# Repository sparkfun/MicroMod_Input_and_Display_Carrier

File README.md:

# SparkFun MicroMod Input and Display Carrier Board
========================================

[*SparkFun MicroMod Input and Display Carrier Board (16985)*](https://www.sparkfun.com/products/16985)

The SparkFun MicroMod Input and Display Carrier Board is a great way to add data and input visibility to your MicroMod project. Want to create your own embedded game? How about displaying data that is remotely collected and transmitted by your SparkFun MicroMod Weather Carrier Board and its processor? This is a great option. 

This carrier board combines a 2.4" TFT display, 6 addressable LEDs, onboard voltage regulator, a 6 pin IO connector, and microSD slot with the M.2 pin connector slot so that it can be used with compatible processor boards in our MicroMod ecosystem. 

Repository Contents
-------------------
* **/Firmware** - Example code specific to the Input and Display Carrier Board.
* **/Hardware** - Eagle design files (.brd, .sch)
* **/Production** - Production panel files (.brd)

Documentation
--------------
* **[Hookup Guide](https://learn.sparkfun.com/tutorials/sparkfun-micromod-input-and-display-carrier-board-hookup-guide)** - Basic hookup guide for the SparkFun MicroMod Input and Display Carrier Board.
* **[SparkFun Graphical Datasheets](https://github.com/sparkfun/Graphical_Datasheets)** -Graphical Datasheets for various SparkFun products.
* **[SparkFun HyperDisplay](https://github.com/sparkfun/SparkFun_HyperDisplay/archive/master.zip)** - Base level HyperDisplay library.
* **[SparkFun HyperDisplay ILI9341 Arduino Library](https://github.com/sparkfun/HyperDisplay_ILI9341_ArduinoLibrary/archive/master.zip)** - Mid level HyperDisplay library.
* **[SparkFun_HyperDisplay 4DLCD-320240 Arduino Library](https://github.com/sparkfun/HyperDisplay_4DLCD-320240_ArduinoLibrary/archive/master.zip)** -  Top level HyperDisplay library for the SparkFun MicroMod Input and Display Carrier Board. This library contains the examples for using the Input and Display Carrier Board.
* **[SparkFun MicroMod Button Arduino Library](https://github.com/sparkfun/SparkFun_MicroMod_Button_Arduino_Library)** - Example library to allow the user to determine if buttons on the board are pressed.  
* **[Getting Started with MicroMod](https://learn.sparkfun.com/tutorials/getting-started-with-micromod)** - A tutorial to help you get started with the MicroMod Ecosystem. 
* **[Designing with MicroMod](https://learn.sparkfun.com/tutorials/designing-with-micromod)** - A tutorial to walk you through the specs of the MicroMod processor and carrier board as well as the basics of incorporating the MicroMod form factor into your own PCB designs.

License Information
-------------------

This product is _**open source**_! 

Please review the LICENSE.md file for license information. 

If you have any questions or concerns on licensing, please contact technical support on our [SparkFun forums](https://forum.sparkfun.com/viewforum.php?f=152).

Distributed as-is; no warranty is given.

- Your friends at SparkFun.

_<COLLABORATION CREDIT>_

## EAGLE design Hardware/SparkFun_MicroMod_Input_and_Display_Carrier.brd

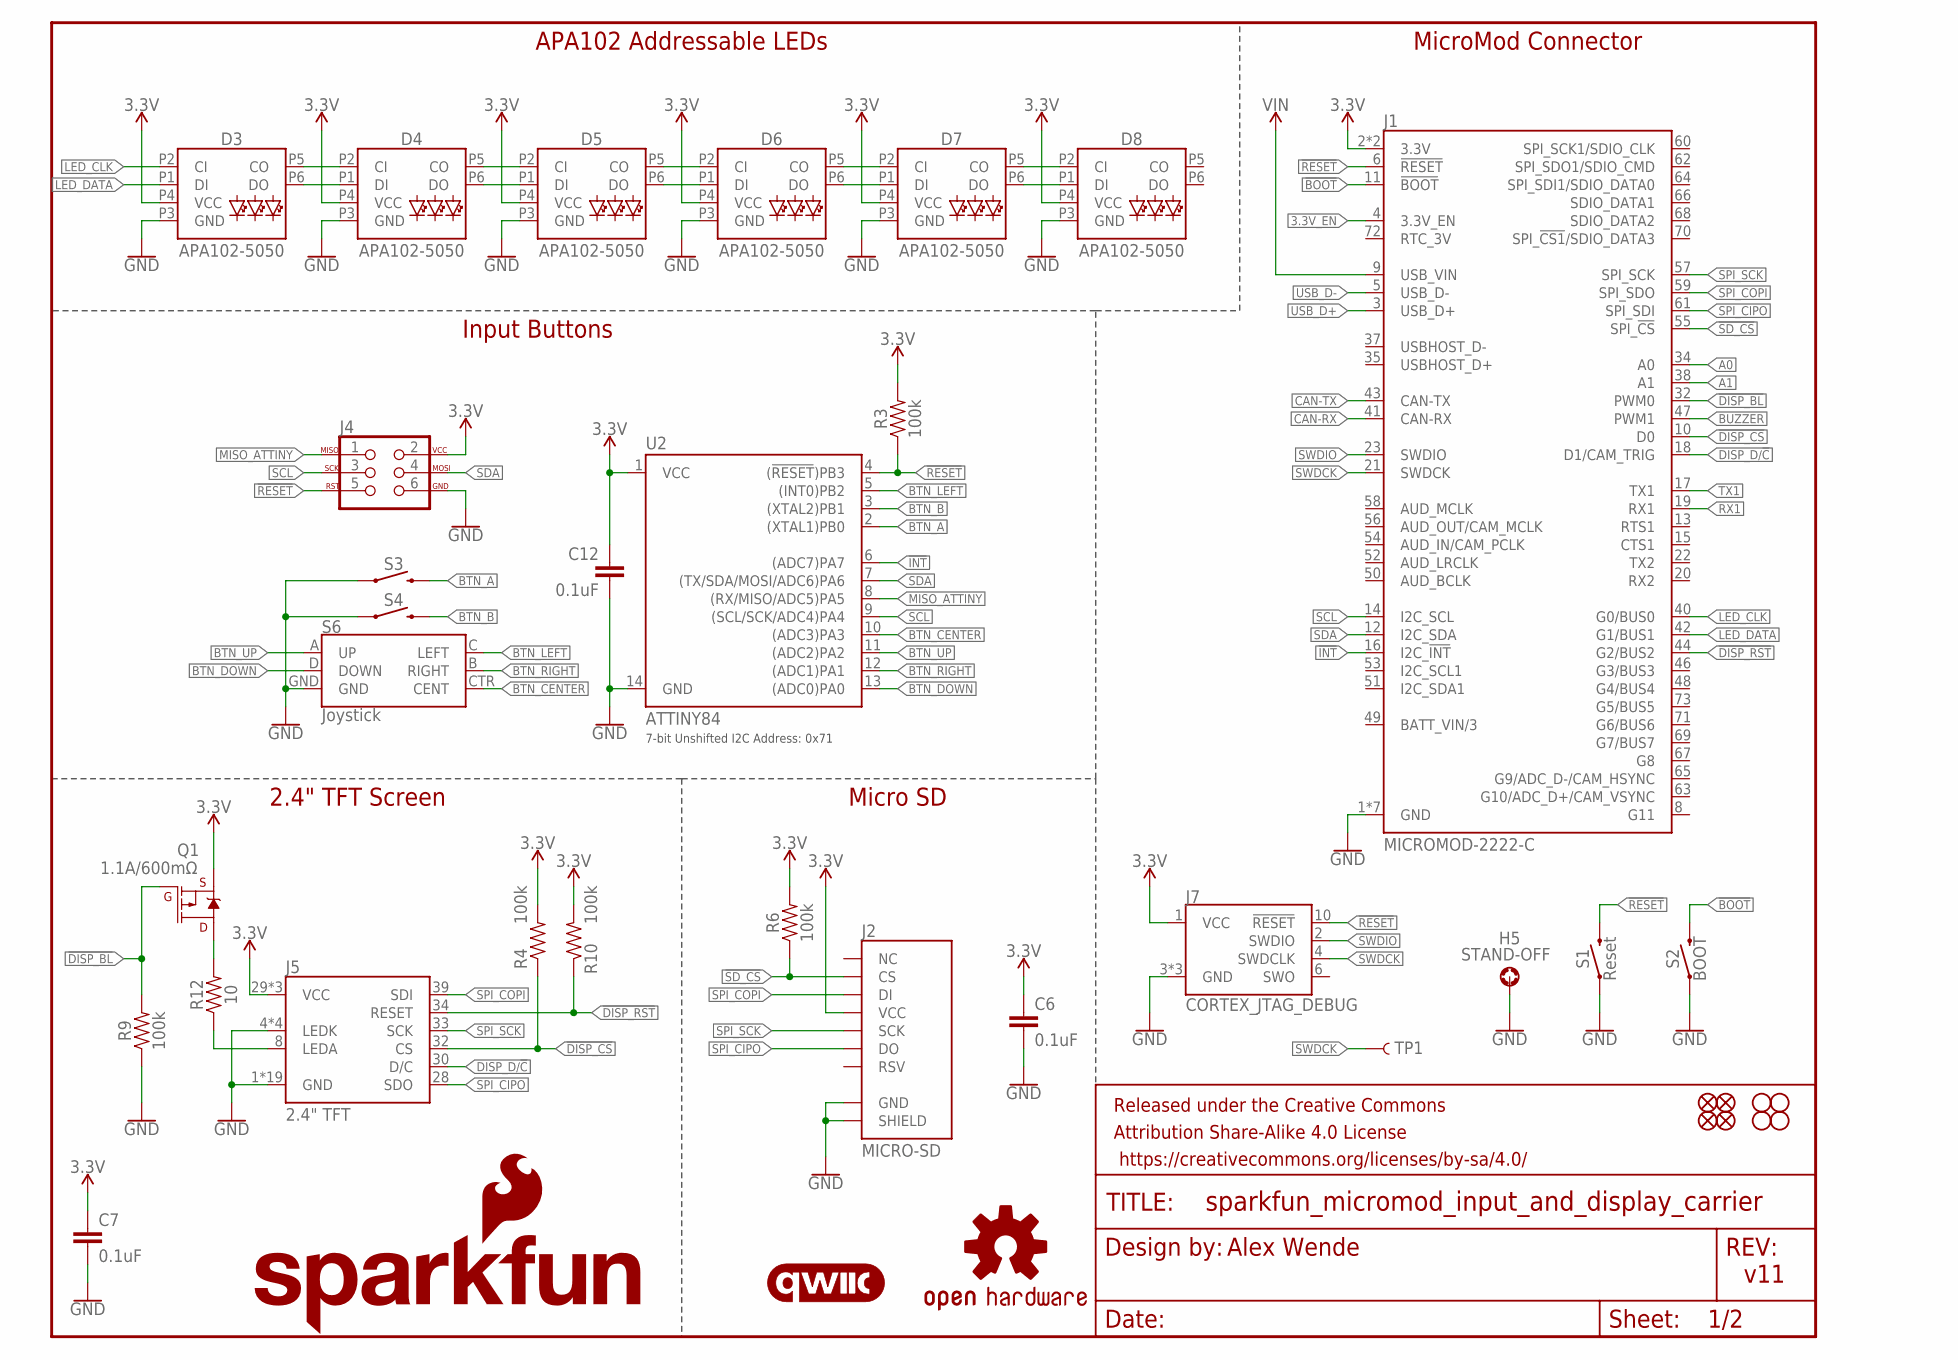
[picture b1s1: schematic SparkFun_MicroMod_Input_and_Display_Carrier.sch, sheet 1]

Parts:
C6, C7, C12: 0.1uF; 0603
D3, D4, D5, D6, D7, D8: APA102-5050
FD1, FD2, FD3, FD4: FIDUCIALUFIDUCIAL; FIDUCIAL-MICRO
FRAME1: FRAME-LETTER; CREATIVE_COMMONS
H1, H2, H3, H4: STAND-OFF
H5: STAND-OFF; STAND-OFF-REFLOW-M2.5
J1: MICROMOD-2222-C; M.2-CONNECTOR-E
J2: MICRO-SD; MICRO-SD-SOCKET
J4: AVR_SPI_PROG_3X2TESTPOINTS; 2X3_TEST_POINTS
J5: 2.4" TFT; FPC05040-17204
J7: CORTEX_JTAG_DEBUG; 2X5-PTH-1.27MM-NO_SILK
LOGO1: SFE_LOGO_NAME_FLAME.2_INCH; SFE_LOGO_NAME_FLAME_.2
LOGO2: QWIIC_LOGO_5MM; QWIIC_5MM
LOGO3: OSHW-LOGOS; OSHW-LOGO-S
Q1: 1.1A/600mΩ; SOT23-3
R3, R4, R6, R9, R10: 100k; 0603
R12: 10; 1206
S1: Reset; TACTILE_SWITCH_SMD_5.2MM
S2: BOOT; TACTILE_SWITCH_SMD_5.2MM
S3, S4: MOMENTARY-SWITCH-SPST-SMD-5.2MM-TALL; TACTILE_SWITCH_SMD_5.2MM
S6: Joystick; JOYSTICK_MINI
TP1: TEST-POINT3; PAD.03X.03
U2: ATTINY84; SO14

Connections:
3.3V: C6.1, C7.1, C12.1, D3.P4 (VCC), D4.P4 (VCC), D5.P4 (VCC), D6.P4 (VCC), D7.P4 (VCC), D8.P4 (VCC), J1.2 (3.3V), J1.74 (3.3V), J2.VCC, J4.2, J5.29 (VCC), J5.31 (VCC), J5.38 (VCC), J7.1 (VCC), Q1.2 (S), R3.2, R4.2, R6.2, R10.2, U2.1 (VCC); also elsewhere on the board
3.3V_EN: J1.4 (3.3V_EN); also elsewhere on the board
!BOOT: J1.11 (!BOOT!), S2.3 (2), S2.4 (2)
!DISP_BL: J1.32 (PWM0), Q1.1 (G), R9.2
!DISP_CS: J1.10 (D0), J5.32 (CS), R4.1
!DISP_RST: J1.44 (G2/BUS2), J5.34 (RESET), R10.1
!INT: J1.16 (I2C_!INT!), U2.6 ((ADC7)PA7)
!RESET: J1.6 (!RESET!), J4.5, J7.10 (!RESET), R3.1, S1.3 (2), S1.4 (2), U2.4 ((!RESET!)PB3)
!SD_CS: J1.55 (SPI_!CS!), J2.CS, R6.1
A0: J1.34 (A0); also elsewhere on the board
A1: J1.38 (A1); also elsewhere on the board
BTN_A: S3.3 (2), U2.2 ((XTAL1)PB0)
BTN_B: S4.3 (2), U2.3 ((XTAL2)PB1)
BTN_CENTER: S6.CTR (CENT), U2.10 ((ADC3)PA3)
BTN_DOWN: S6.D (DOWN), U2.13 ((ADC0)PA0)
BTN_LEFT: S6.C (LEFT), U2.5 ((INT0)PB2)
BTN_RIGHT: S6.B (RIGHT), U2.12 ((ADC1)PA1)
BTN_UP: S6.A (UP), U2.11 ((ADC2)PA2)
BUZZER: J1.47 (PWM1); also elsewhere on the board
CAN-RX: J1.41 (CAN-RX); also elsewhere on the board
CAN-TX: J1.43 (CAN-TX); also elsewhere on the board
DISP_D/!C: J1.18 (D1/CAM_TRIG), J5.30 (D/C)
GND: C6.2, C7.2, C12.2, D3.P3 (GND), D4.P3 (GND), D5.P3 (GND), D6.P3 (GND), D7.P3 (GND), D8.P3 (GND), H5.1, J1.1 (GND), J1.7 (GND), J1.33 (GND), J1.36 (GND), J1.39 (GND), J1.45 (GND), J1.75 (GND), J2.CD1 (SHIELD), J2.GND, J4.6, J5.1 (GND), J5.4 (LEDK), J5.5 (LEDK), J5.6 (LEDK), J5.7 (LEDK), J5.11 (GND), J5.12 (GND), J5.13 (GND), J5.14 (GND), J5.15 (GND), J5.16 (GND), J5.17 (GND), J5.18 (GND), J5.19 (GND), J5.20 (GND), J5.21 (GND), J5.22 (GND), J5.23 (GND), J5.24 (GND), J5.25 (GND), J5.26 (GND), J5.27 (GND), J5.40 (GND), J7.3 (GND), J7.5 (GND), J7.9 (GND), R9.1, S1.1, S1.2 (1), S2.1, S2.2 (1), S3.1, S4.1, S6.GND, U2.14 (GND); also elsewhere on the board
LED_CLK: D3.P2 (CI), J1.40 (G0/BUS0)
LED_DATA: D3.P1 (DI), J1.42 (G1/BUS1)
MISO_ATTINY: J4.1, U2.8 ((RX/MISO/ADC5)PA5)
unnamed: J5.8 (LEDA), R12.1
unnamed: Q1.3 (D), R12.2
unnamed: D3.P5 (CO), D4.P2 (CI)
unnamed: D3.P6 (DO), D4.P1 (DI)
unnamed: D4.P5 (CO), D5.P2 (CI)
unnamed: D4.P6 (DO), D5.P1 (DI)
unnamed: D5.P5 (CO), D6.P2 (CI)
unnamed: D5.P6 (DO), D6.P1 (DI)
unnamed: D6.P5 (CO), D7.P2 (CI)
unnamed: D6.P6 (DO), D7.P1 (DI)
unnamed: D7.P5 (CO), D8.P2 (CI)
unnamed: D7.P6 (DO), D8.P1 (DI)
RX1: J1.19 (RX1); also elsewhere on the board
SCL: J1.14 (I2C_SCL), J4.3, U2.9 ((SCL/SCK/ADC4)PA4); also elsewhere on the board
SDA: J1.12 (I2C_SDA), J4.4, U2.7 ((TX/SDA/MOSI/ADC6)PA6); also elsewhere on the board
SPI_CIPO: J1.61 (SPI_SDI), J2.DO, J5.28 (SDO)
SPI_COPI: J1.59 (SPI_SDO), J2.DI, J5.39 (SDI)
SPI_SCK: J1.57 (SPI_SCK), J2.SCLK (SCK), J5.33 (SCK)
SWDCK: J1.21 (SWDCK), J7.4 (SWDCLK), TP1.P$1
SWDIO: J1.23 (SWDIO), J7.2 (SWDIO)
TX1: J1.17 (TX1); also elsewhere on the board
USB_D+: J1.3 (USB_D+); also elsewhere on the board
USB_D-: J1.5 (USB_D-); also elsewhere on the board
VIN: J1.9 (USB_VIN); also elsewhere on the board

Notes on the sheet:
7-bit Unshifted I2C Address: 0x71
Alex Wende
v11
Micro SD
2.4" TFT Screen
Input Buttons
APA102 Addressable LEDs
MicroMod Connector

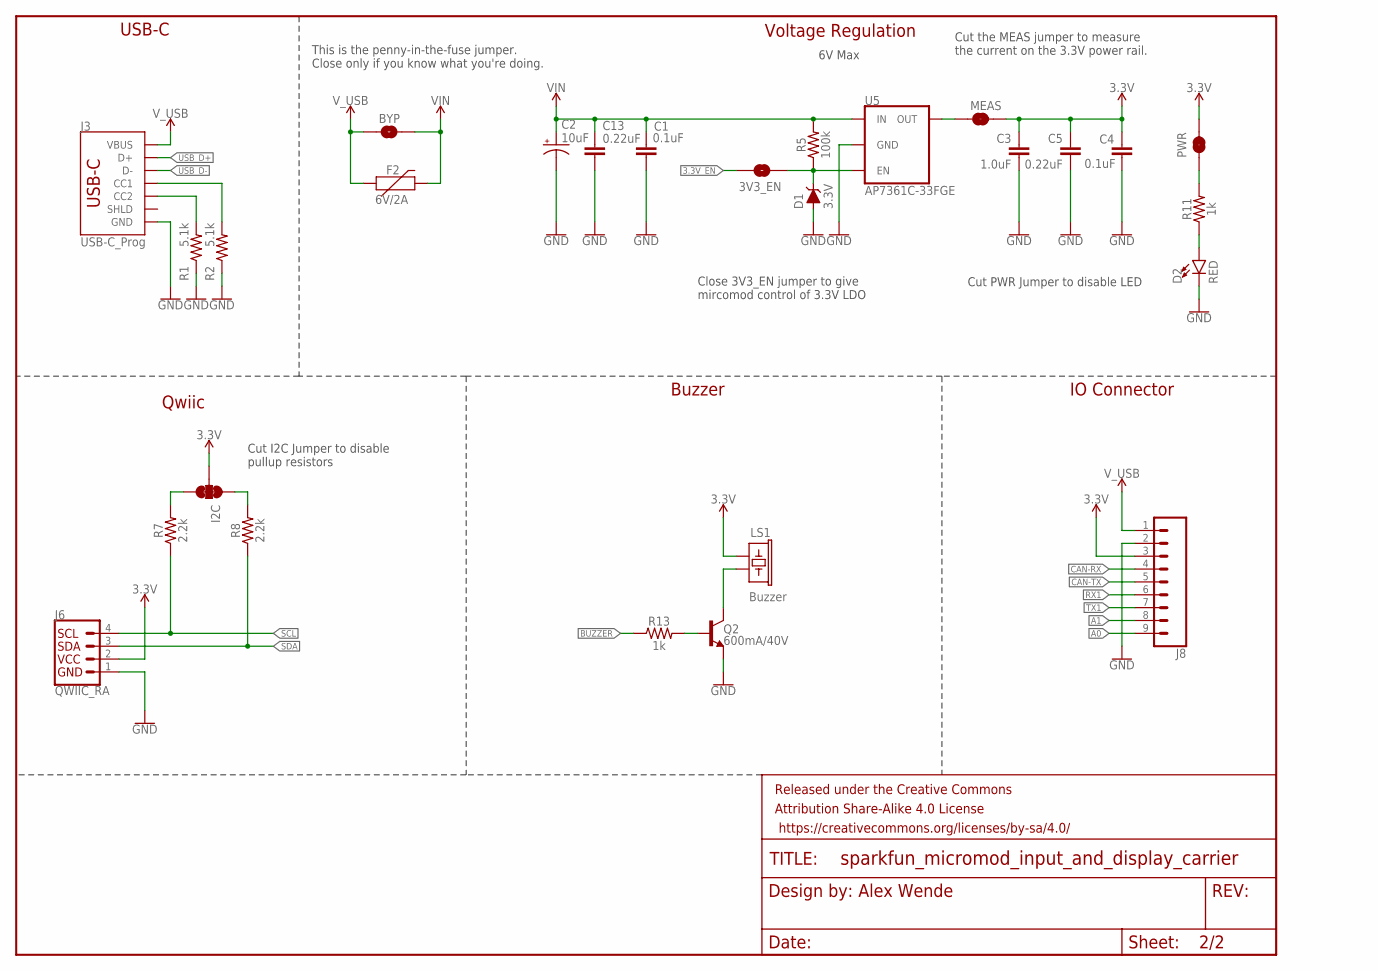
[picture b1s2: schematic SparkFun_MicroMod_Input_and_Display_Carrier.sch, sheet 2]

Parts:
3V3_EN: JUMPER-SMT_2_NO_SILK; SMT-JUMPER_2_NO_SILK
BYP: JUMPER-SMT_2_NO_SILK; SMT-JUMPER_2_NO_SILK
C1, C4: 0.1uF; 0603
C2: 10uF; EIA3216
C3: 1.0uF; 0603
C5, C13: 0.22uF; 0603
D1: 3.3V; SOD-323
D2: RED; LED-0603
F2: 6V/2A; 1210
FRAME2: FRAME-LETTERNO_PACKAGE; DUMMY
I2C: JUMPER-SMT_3_2-NC_TRACE_SILK; SMT-JUMPER_3_2-NC_TRACE_SILK
J3: USB-C_Prog; USB-C-16P-2LAYER-PADS
J6: QWIIC_RA; JST04_1MM_RA
J8: CONN_09NO_SILK; 1X09_NO_SILK
LS1: Buzzer; BUZZER-CCV
MEAS: JUMPER-COMBO_2_NC_TRACE; COMBO-JUMPER_2_NC_TRACE
PWR: JUMPER-SMT_2_NC_TRACE_SILK; SMT-JUMPER_2_NC_TRACE_SILK
Q2: 600mA/40V; SOT23-3
R1, R2: 5.1k; 0603
R5: 100k; 0603
R7, R8: 2.2k; 0603
R11, R13: 1k; 0603
U5: AP7361C-33FGE; UDFN-8

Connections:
3.3V: C3.1, C4.1, C5.1, I2C.2, J6.2, J8.3, LS1.+ (1), MEAS.2, MEAS.4 (2), PWR.2; also elsewhere on the board
3.3V_EN: 3V3_EN.1; also elsewhere on the board
A0: J8.9; also elsewhere on the board
A1: J8.8; also elsewhere on the board
BUZZER: R13.1; also elsewhere on the board
CAN-RX: J8.4; also elsewhere on the board
CAN-TX: J8.5; also elsewhere on the board
ENABLE: 3V3_EN.2, D1.C, R5.1, U5.5 (EN)
GND: C1.2, C2.-, C3.2, C4.2, C5.2, C13.2, D1.A, D2.C, J3.GND, J3.GND2 (GND), J6.1, J8.2, Q2.2 (E), R1.1, R2.1, U5.4 (GND), U5.EP (GND); also elsewhere on the board
unnamed: I2C.3, R7.2
unnamed: I2C.1, R8.2
unnamed: LS1.- (2), Q2.3 (C)
unnamed: Q2.1 (B), R13.2
unnamed: J3.A5 (CC1), R2.2
unnamed: J3.B5 (CC2), R1.2
unnamed: PWR.1, R11.2
unnamed: D2.A, R11.1
unnamed: MEAS.1, MEAS.3 (1), U5.1 (OUT)
RX1: J8.6; also elsewhere on the board
SCL: J6.4, R7.1; also elsewhere on the board
SDA: J6.3, R8.1; also elsewhere on the board
TX1: J8.7; also elsewhere on the board
USB_D+: J3.A6 (D+), J3.B6 (D+); also elsewhere on the board
USB_D-: J3.A7 (D-), J3.B7 (D-); also elsewhere on the board
VIN: BYP.2, C1.1, C2.+, C13.1, F2.2, R5.2, U5.8 (IN); also elsewhere on the board
V_USB: BYP.1, F2.1, J3.VBUS1 (VBUS), J3.VBUS2 (VBUS), J8.1

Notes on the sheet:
This is the penny-in-the-fuse jumper. Close only if you know what you're doing.
Voltage Regulation
USB-C
Alex Wende
Qwiic
Cut PWR Jumper to disable LED
Cut I2C Jumper to disable pullup resistors
Close 3V3_EN jumper to give mircomod control of 3.3V LDO
Buzzer
IO Connector
6V Max
Cut the MEAS jumper to measure the current on the 3.3V power rail.

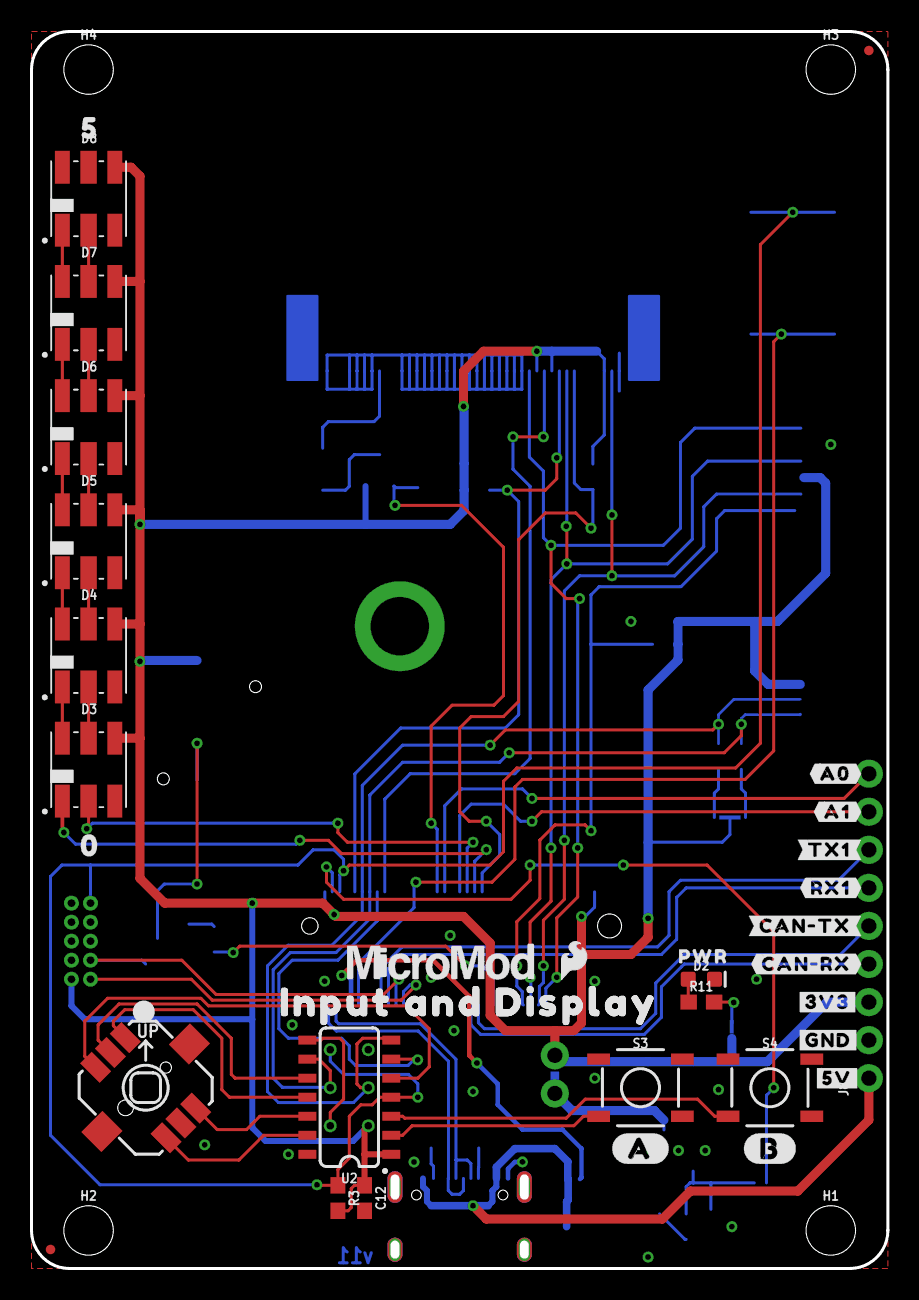
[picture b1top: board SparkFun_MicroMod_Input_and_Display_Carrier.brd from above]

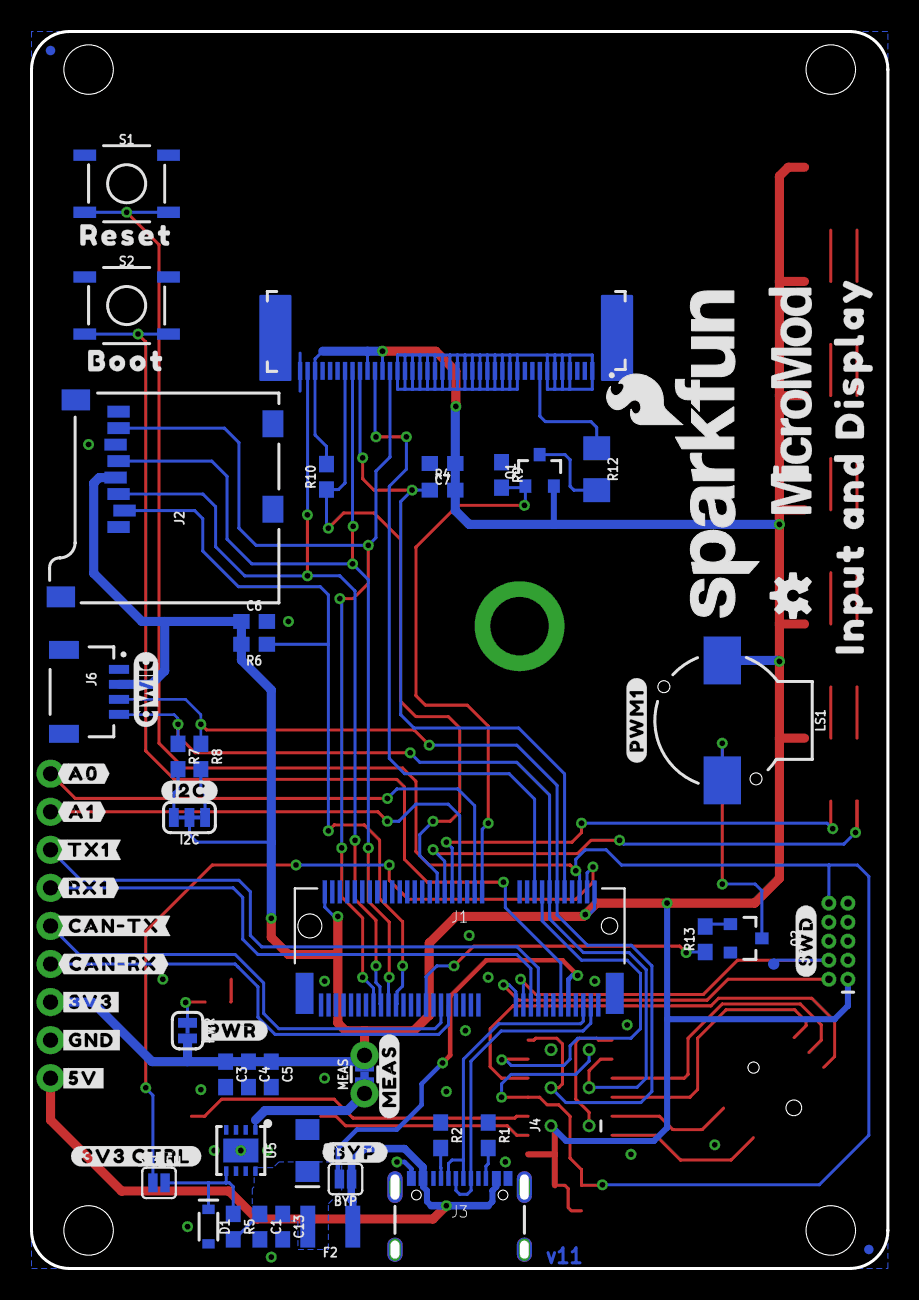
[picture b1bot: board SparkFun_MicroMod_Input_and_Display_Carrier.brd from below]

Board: 2 copper layers, 56.8 x 82.2 mm, 107 parts (66 on the bottom side), 61 nets.

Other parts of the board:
U$1: MICROMOD_LOGO_.5
U$2, U$16, U$17: INPUT_AND_DISPLAY0
U$3: SFE_LOGO_FLAME_.1
U$4: BOOT0
U$5: #A#0
U$6: #B#0
U$7: 00
U$8: 50
U$9: RESET0
U$10: MICROMOD_LOGO_.6
U$11: #MEAS#0
U$12: #I2C#0
U$13: PWR0
U$14: #BYP#0
U$15: #SWD#0
U$18, U$38: #5V#0
U$19: #PWR#0
U$20: #3V3_CTRL#0
U$21: #PWM1#0
U$22, U$23: #A0#0
U$24, U$25: #A1#0
U$26, U$27: #TX1#0
U$28, U$31: #3V3#0
U$29, U$30: #GND#0
U$32, U$33: #RX1#0
U$34, U$35: #CAN#RX#0
U$36, U$37: #CAN#TX#0

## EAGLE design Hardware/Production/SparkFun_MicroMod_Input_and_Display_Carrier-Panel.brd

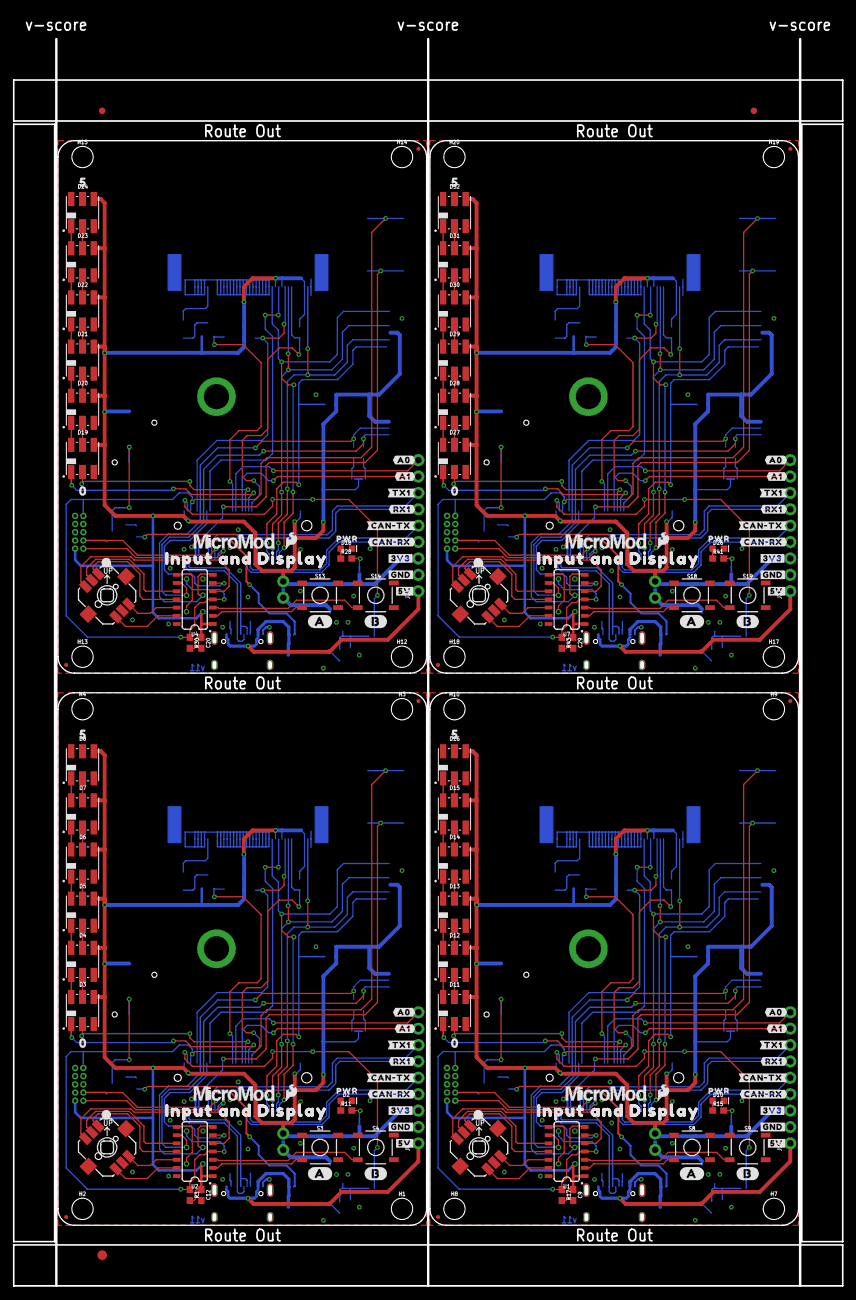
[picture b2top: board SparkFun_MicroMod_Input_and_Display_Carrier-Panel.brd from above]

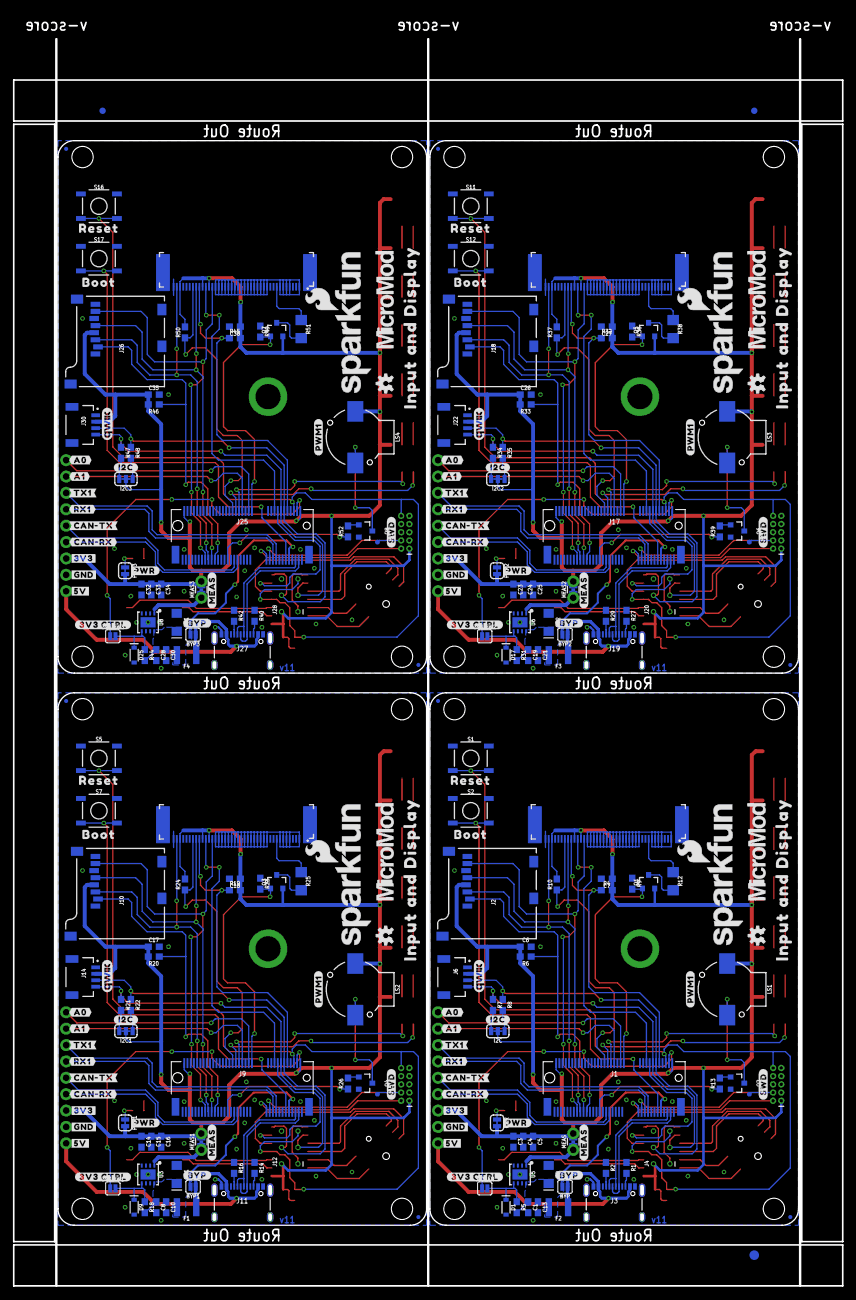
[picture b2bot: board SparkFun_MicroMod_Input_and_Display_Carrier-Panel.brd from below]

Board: 2 copper layers, 128.2 x 196.9 mm, 434 parts (267 on the bottom side), 244 nets.

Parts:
3V3_EN, 3V3_EN1, 3V3_EN2, 3V3_EN3: SMT-JUMPER_2_NO_SILK
BYP, BYP1, BYP2, BYP3: JUMPER-SMT_2_NO_SILK; SMT-JUMPER_2_NO_SILK
C1, C4, C6, C7, C8, C9, C12, C15, C17, C18, C19, C20, C24, C26, C27, C28, C29, C33, C35, C36: 0.1uF; 0603
C2, C11, C22, C31: 10uF; EIA3216
C3, C14, C23, C32: 1.0uF; 0603
C5, C10, C13, C16, C21, C25, C30, C34: 0.22uF; 0603
D1, D9, D17, D25: 3.3V; SOD-323
D2, D10, D18, D26: RED; LED-0603
D3, D4, D5, D6, D7, D8, D11, D12, D13, D14, D15, D16, D19, D20, D21, D22, D23, D24, D27, D28, D29, D30, D31, D32: APA102-5050
E$1, E$2, E$3, E$4: FIDUCIAL-1X2
E$5, E$6: FIDUCIAL-1.5X3
F1, F2, F3, F4: 6V/2A; 1210
FD1, FD2, FD3, FD4, FD5, FD6, FD7, FD8, FD9, FD10, FD11, FD12, FD13, FD14, FD15, FD16: FIDUCIALUFIDUCIAL; FIDUCIAL-MICRO
FRAME1, FRAME3, FRAME5, FRAME7: FRAME-LETTER; CREATIVE_COMMONS
FRAME2, FRAME4, FRAME6, FRAME8: FRAME-LETTERNO_PACKAGE; DUMMY
H1, H2, H3, H4, H7, H8, H9, H10, H12, H13, H14, H15, H17, H18, H19, H20: STAND-OFF
H5, H6, H11, H16: STAND-OFF; STAND-OFF-REFLOW-M2.5
I2C, I2C1, I2C2, I2C3: SMT-JUMPER_3_2-NC_TRACE_SILK
J1, J9, J17, J25: MICROMOD-2222-C; M.2-CONNECTOR-E
J2, J10, J18, J26: MICRO-SD; MICRO-SD-SOCKET
J3, J11, J19, J27: USB-C_Prog; USB-C-16P-2LAYER-PADS
J4, J12, J20, J28: AVR_SPI_PROG_3X2TESTPOINTS; 2X3_TEST_POINTS
J5, J13, J21, J29: 2.4" TFT; FPC05040-17204
J6, J14, J22, J30: QWIIC_RA; JST04_1MM_RA
J7, J15, J23, J31: CORTEX_JTAG_DEBUG; 2X5-PTH-1.27MM-NO_SILK
J8, J16, J24, J32: 1X09_NO_SILK
LOGO1, LOGO4, LOGO7, LOGO10: SFE_LOGO_NAME_FLAME.2_INCH; SFE_LOGO_NAME_FLAME_.2
LOGO2, LOGO5, LOGO8, LOGO11: QWIIC_LOGO_5MM; QWIIC_5MM
LOGO3, LOGO6, LOGO9, LOGO12: OSHW-LOGOS; OSHW-LOGO-S
LS1, LS2, LS3, LS4: Buzzer; BUZZER-CCV
MEAS, MEAS1, MEAS2, MEAS3: COMBO-JUMPER_2_NC_TRACE
PWR, PWR1, PWR2, PWR3: SMT-JUMPER_2_NC_TRACE_SILK
Q1, Q3, Q5, Q7: 1.1A/600mΩ; SOT23-3
Q2, Q4, Q6, Q8: 600mA/40V; SOT23-3
R1, R2, R14, R16, R27, R29, R40, R42: 5.1k; 0603
R3, R4, R5, R6, R9, R10, R17, R18, R19, R20, R23, R24, R30, R31, R32, R33, R36, R37, R43, R44, R45, R46, R49, R50: 100k; 0603
R7, R8, R21, R22, R34, R35, R47, R48: 2.2k; 0603
R11, R13, R15, R26, R28, R39, R41, R52: 1k; 0603
R12, R25, R38, R51: 10; 1206
S1, S5, S11, S16: Reset; TACTILE_SWITCH_SMD_5.2MM
S2, S7, S12, S17: BOOT; TACTILE_SWITCH_SMD_5.2MM
S3, S4, S8, S9, S13, S14, S18, S19: MOMENTARY-SWITCH-SPST-SMD-5.2MM-TALL; TACTILE_SWITCH_SMD_5.2MM
S6, S10, S15, S20: Joystick; JOYSTICK_MINI
TP1, TP2, TP3, TP4: PAD.03X.03
U1, U2, U4, U7: ATTINY84; SO14
U3, U5, U6, U8: AP7361C-33FGE; UDFN-8
U$1, U$39, U$77, U$115: MICROMOD_LOGO_.5
U$2, U$16, U$17, U$40, U$54, U$55, U$78, U$92, U$93, U$116, U$130, U$131: INPUT_AND_DISPLAY0
U$3, U$45, U$83, U$121: SFE_LOGO_FLAME_.1
U$4, U$46, U$84, U$122: BOOT0
U$5, U$41, U$79, U$117: #A#0
U$6, U$42, U$80, U$118: #B#0
U$7, U$43, U$81, U$119: 00
U$8, U$44, U$82, U$120: 50
U$9, U$47, U$85, U$123: RESET0
U$10, U$51, U$89, U$127: MICROMOD_LOGO_.6
U$11, U$48, U$86, U$124: #MEAS#0
U$12, U$49, U$87, U$125: #I2C#0
U$13, U$50, U$88, U$126: PWR0
U$14, U$52, U$90, U$128: #BYP#0
U$15, U$53, U$91, U$129: #SWD#0
U$18, U$38, U$75, U$76, U$113, U$114, U$151, U$152: #5V#0
U$19, U$56, U$94, U$132: #PWR#0
U$20, U$57, U$95, U$133: #3V3_CTRL#0
U$21, U$58, U$96, U$134: #PWM1#0
U$22, U$23, U$63, U$64, U$101, U$102, U$139, U$140: #A0#0
U$24, U$25, U$65, U$66, U$103, U$104, U$141, U$142: #A1#0
U$26, U$27, U$67, U$68, U$105, U$106, U$143, U$144: #TX1#0
U$28, U$31, U$59, U$62, U$97, U$100, U$135, U$138: #3V3#0
U$29, U$30, U$60, U$61, U$98, U$99, U$136, U$137: #GND#0
U$32, U$33, U$69, U$70, U$107, U$108, U$145, U$146: #RX1#0
U$34, U$35, U$71, U$72, U$109, U$110, U$147, U$148: #CAN#RX#0
U$36, U$37, U$73, U$74, U$111, U$112, U$149, U$150: #CAN#TX#0

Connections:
3.3V: C3.1, C4.1, C5.1, C6.1, C7.1, C12.1, D3.P4, D4.P4, D5.P4, D6.P4, D7.P4, D8.P4, I2C.2, J1.2, J1.74, J2.VCC, J4.2, J5.29, J5.31, J5.38, J6.2, J7.1, J8.3, LS1.+, MEAS.2, MEAS.4, PWR.2, Q1.2, R3.2, R4.2, R6.2, R10.2, U2.1
3.3V1: C9.1, C14.1, C15.1, C16.1, C17.1, C18.1, D11.P4, D12.P4, D13.P4, D14.P4, D15.P4, D16.P4, I2C1.2, J9.2, J9.74, J10.VCC, J12.2, J13.29, J13.31, J13.38, J14.2, J15.1, J16.3, LS2.+, MEAS1.2, MEAS1.4, PWR1.2, Q3.2, R17.2, R19.2, R20.2, R24.2, U1.1
3.3V2: C20.1, C23.1, C24.1, C25.1, C26.1, C27.1, D19.P4, D20.P4, D21.P4, D22.P4, D23.P4, D24.P4, I2C2.2, J17.2, J17.74, J18.VCC, J20.2, J21.29, J21.31, J21.38, J22.2, J23.1, J24.3, LS3.+, MEAS2.2, MEAS2.4, PWR2.2, Q5.2, R30.2, R32.2, R33.2, R37.2, U4.1
3.3V3: C29.1, C32.1, C33.1, C34.1, C35.1, C36.1, D27.P4, D28.P4, D29.P4, D30.P4, D31.P4, D32.P4, I2C3.2, J25.2, J25.74, J26.VCC, J28.2, J29.29, J29.31, J29.38, J30.2, J31.1, J32.3, LS4.+, MEAS3.2, MEAS3.4, PWR3.2, Q7.2, R43.2, R45.2, R46.2, R50.2, U7.1
3.3V_EN: 3V3_EN.1, J1.4
3.3V_EN1: 3V3_EN1.1, J9.4
3.3V_EN2: 3V3_EN2.1, J17.4
3.3V_EN3: 3V3_EN3.1, J25.4
!BOOT: J1.11, S2.3, S2.4
!BOOT1: J9.11, S7.3, S7.4
!BOOT2: J17.11, S12.3, S12.4
!BOOT3: J25.11, S17.3, S17.4
!DISP_BL: J1.32, Q1.1, R9.2
!DISP_BL1: J9.32, Q3.1, R23.2
!DISP_BL2: J17.32, Q5.1, R36.2
!DISP_BL3: J25.32, Q7.1, R49.2
!DISP_CS: J1.10, J5.32, R4.1
!DISP_CS1: J9.10, J13.32, R19.1
!DISP_CS2: J17.10, J21.32, R32.1
!DISP_CS3: J25.10, J29.32, R45.1
!DISP_RST: J1.44, J5.34, R10.1
!DISP_RST1: J9.44, J13.34, R24.1
!DISP_RST2: J17.44, J21.34, R37.1
!DISP_RST3: J25.44, J29.34, R50.1
!INT: J1.16, U2.6
!INT1: J9.16, U1.6
!INT2: J17.16, U4.6
!INT3: J25.16, U7.6
!RESET: J1.6, J4.5, J7.10, R3.1, S1.3, S1.4, U2.4
!RESET1: J9.6, J12.5, J15.10, R17.1, S5.3, S5.4, U1.4
!RESET2: J17.6, J20.5, J23.10, R30.1, S11.3, S11.4, U4.4
!RESET3: J25.6, J28.5, J31.10, R43.1, S16.3, S16.4, U7.4
!SD_CS: J1.55, J2.CS, R6.1
!SD_CS1: J9.55, J10.CS, R20.1
!SD_CS2: J17.55, J18.CS, R33.1
!SD_CS3: J25.55, J26.CS, R46.1
A0: J1.34, J8.9
A1: J1.38, J8.8
A2: J9.34, J16.9
A3: J9.38, J16.8
A4: J17.34, J24.9
A5: J17.38, J24.8
A6: J25.34, J32.9
A7: J25.38, J32.8
BTN_A: S3.3, U2.2
BTN_A1: S8.3, U1.2
BTN_A2: S13.3, U4.2
BTN_A3: S18.3, U7.2
BTN_B: S4.3, U2.3
BTN_B1: S9.3, U1.3
BTN_B2: S14.3, U4.3
BTN_B3: S19.3, U7.3
BTN_CENTER: S6.CTR, U2.10
BTN_CENTER1: S10.CTR, U1.10
BTN_CENTER2: S15.CTR, U4.10
BTN_CENTER3: S20.CTR, U7.10
BTN_DOWN: S6.D, U2.13
BTN_DOWN1: S10.D, U1.13
BTN_DOWN2: S15.D, U4.13
BTN_DOWN3: S20.D, U7.13
BTN_LEFT: S6.C, U2.5
BTN_LEFT1: S10.C, U1.5
BTN_LEFT2: S15.C, U4.5
BTN_LEFT3: S20.C, U7.5
BTN_RIGHT: S6.B, U2.12
BTN_RIGHT1: S10.B, U1.12
BTN_RIGHT2: S15.B, U4.12
BTN_RIGHT3: S20.B, U7.12
BTN_UP: S6.A, U2.11
BTN_UP1: S10.A, U1.11
BTN_UP2: S15.A, U4.11
BTN_UP3: S20.A, U7.11
BUZZER: J1.47, R13.1
BUZZER1: J9.47, R26.1
BUZZER2: J17.47, R39.1
BUZZER3: J25.47, R52.1
CAN-RX: J1.41, J8.4
CAN-RX1: J9.41, J16.4
CAN-RX2: J17.41, J24.4
CAN-RX3: J25.41, J32.4
CAN-TX: J1.43, J8.5
CAN-TX1: J9.43, J16.5
CAN-TX2: J17.43, J24.5
CAN-TX3: J25.43, J32.5
DISP_D/!C: J1.18, J5.30
DISP_D/!C1: J9.18, J13.30
DISP_D/!C2: J17.18, J21.30
DISP_D/!C3: J25.18, J29.30
ENABLE: 3V3_EN.2, D1.C, R5.1, U5.5
ENABLE1: 3V3_EN1.2, D9.C, R18.1, U3.5
ENABLE2: 3V3_EN2.2, D17.C, R31.1, U6.5
ENABLE3: 3V3_EN3.2, D25.C, R44.1, U8.5
GND: C1.2, C2.-, C3.2, C4.2, C5.2, C6.2, C7.2, C12.2, C13.2, D1.A, D2.C, D3.P3, D4.P3, D5.P3, D6.P3, D7.P3, D8.P3, H5.1, J1.1, J1.7, J1.33, J1.36, J1.39, J1.45, J1.75, J2.CD1, J2.GND, J3.GND, J3.GND2, J4.6, J5.1, J5.4, J5.5, J5.6, J5.7, J5.11, J5.12, J5.13, J5.14, J5.15, J5.16, J5.17, J5.18, J5.19, J5.20, J5.21, J5.22, J5.23, J5.24, J5.25, J5.26, J5.27, J5.40, J6.1, J7.3, J7.5, J7.9, J8.2, Q2.2, R1.1, R2.1, R9.1, S1.1, S1.2, S2.1, S2.2, S3.1, S4.1, S6.GND, U2.14, U5.4, U5.EP
GND1: C8.2, C9.2, C10.2, C11.-, C14.2, C15.2, C16.2, C17.2, C18.2, D9.A, D10.C, D11.P3, D12.P3, D13.P3, D14.P3, D15.P3, D16.P3, H6.1, J9.1, J9.7, J9.33, J9.36, J9.39, J9.45, J9.75, J10.CD1, J10.GND, J11.GND, J11.GND2, J12.6, J13.1, J13.4, J13.5, J13.6, J13.7, J13.11, J13.12, J13.13, J13.14, J13.15, J13.16, J13.17, J13.18, J13.19, J13.20, J13.21, J13.22, J13.23, J13.24, J13.25, J13.26, J13.27, J13.40, J14.1, J15.3, J15.5, J15.9, J16.2, Q4.2, R14.1, R16.1, R23.1, S5.1, S5.2, S7.1, S7.2, S8.1, S9.1, S10.GND, U1.14, U3.4, U3.EP
GND2: C19.2, C20.2, C21.2, C22.-, C23.2, C24.2, C25.2, C26.2, C27.2, D17.A, D18.C, D19.P3, D20.P3, D21.P3, D22.P3, D23.P3, D24.P3, H11.1, J17.1, J17.7, J17.33, J17.36, J17.39, J17.45, J17.75, J18.CD1, J18.GND, J19.GND, J19.GND2, J20.6, J21.1, J21.4, J21.5, J21.6, J21.7, J21.11, J21.12, J21.13, J21.14, J21.15, J21.16, J21.17, J21.18, J21.19, J21.20, J21.21, J21.22, J21.23, J21.24, J21.25, J21.26, J21.27, J21.40, J22.1, J23.3, J23.5, J23.9, J24.2, Q6.2, R27.1, R29.1, R36.1, S11.1, S11.2, S12.1, S12.2, S13.1, S14.1, S15.GND, U4.14, U6.4, U6.EP
GND3: C28.2, C29.2, C30.2, C31.-, C32.2, C33.2, C34.2, C35.2, C36.2, D25.A, D26.C, D27.P3, D28.P3, D29.P3, D30.P3, D31.P3, D32.P3, H16.1, J25.1, J25.7, J25.33, J25.36, J25.39, J25.45, J25.75, J26.CD1, J26.GND, J27.GND, J27.GND2, J28.6, J29.1, J29.4, J29.5, J29.6, J29.7, J29.11, J29.12, J29.13, J29.14, J29.15, J29.16, J29.17, J29.18, J29.19, J29.20, J29.21, J29.22, J29.23, J29.24, J29.25, J29.26, J29.27, J29.40, J30.1, J31.3, J31.5, J31.9, J32.2, Q8.2, R40.1, R42.1, R49.1, S16.1, S16.2, S17.1, S17.2, S18.1, S19.1, S20.GND, U7.14, U8.4, U8.EP
LED_CLK: D3.P2, J1.40
LED_CLK1: D11.P2, J9.40
LED_CLK2: D19.P2, J17.40
LED_CLK3: D27.P2, J25.40
LED_DATA: D3.P1, J1.42
LED_DATA1: D11.P1, J9.42
LED_DATA2: D19.P1, J17.42
LED_DATA3: D27.P1, J25.42
MISO_ATTINY: J4.1, U2.8
MISO_ATTINY1: J12.1, U1.8
MISO_ATTINY2: J20.1, U4.8
MISO_ATTINY3: J28.1, U7.8
unnamed: I2C.3, R7.2
unnamed: I2C.1, R8.2
unnamed: J5.8, R12.1
unnamed: Q1.3, R12.2
unnamed: LS1.-, Q2.3
unnamed: Q2.1, R13.2
unnamed: J11.A5, R16.2
unnamed: J11.B5, R14.2
unnamed: PWR1.1, R15.2
unnamed: D10.A, R15.1
unnamed: D3.P5, D4.P2
unnamed: MEAS1.1, MEAS1.3, U3.1
unnamed: D11.P5, D12.P2
unnamed: D3.P6, D4.P1
unnamed: D11.P6, D12.P1
unnamed: D12.P5, D13.P2
unnamed: D12.P6, D13.P1
unnamed: D13.P5, D14.P2
unnamed: J3.A5, R2.2
unnamed: J3.B5, R1.2
unnamed: PWR.1, R11.2
unnamed: D2.A, R11.1
unnamed: MEAS.1, MEAS.3, U5.1
unnamed: D4.P5, D5.P2
unnamed: D4.P6, D5.P1
unnamed: D5.P5, D6.P2
unnamed: D5.P6, D6.P1
unnamed: D6.P5, D7.P2
unnamed: D6.P6, D7.P1
unnamed: D7.P5, D8.P2
unnamed: D7.P6, D8.P1
unnamed: D13.P6, D14.P1
unnamed: D14.P5, D15.P2
unnamed: D14.P6, D15.P1
unnamed: D15.P5, D16.P2
unnamed: D15.P6, D16.P1
unnamed: I2C1.3, R21.2
unnamed: I2C1.1, R22.2
unnamed: J13.8, R25.1
unnamed: Q3.3, R25.2
unnamed: LS2.-, Q4.3
unnamed: Q4.1, R26.2
unnamed: J19.A5, R29.2
unnamed: J19.B5, R27.2
unnamed: PWR2.1, R28.2
unnamed: D18.A, R28.1
unnamed: MEAS2.1, MEAS2.3, U6.1
unnamed: D19.P5, D20.P2
unnamed: D19.P6, D20.P1
unnamed: D20.P5, D21.P2
unnamed: D20.P6, D21.P1
unnamed: D21.P5, D22.P2
unnamed: D21.P6, D22.P1
unnamed: D22.P5, D23.P2
unnamed: D22.P6, D23.P1
unnamed: D23.P5, D24.P2
unnamed: D23.P6, D24.P1
unnamed: I2C2.3, R34.2
unnamed: I2C2.1, R35.2
unnamed: J21.8, R38.1
unnamed: Q5.3, R38.2
unnamed: LS3.-, Q6.3
unnamed: Q6.1, R39.2
unnamed: J27.A5, R42.2
unnamed: J27.B5, R40.2
unnamed: PWR3.1, R41.2
unnamed: D26.A, R41.1
unnamed: MEAS3.1, MEAS3.3, U8.1
unnamed: D27.P5, D28.P2
unnamed: D27.P6, D28.P1
unnamed: D28.P5, D29.P2
unnamed: D28.P6, D29.P1
unnamed: D29.P5, D30.P2
unnamed: D29.P6, D30.P1
unnamed: D30.P5, D31.P2
unnamed: D30.P6, D31.P1
unnamed: D31.P5, D32.P2
unnamed: D31.P6, D32.P1
unnamed: I2C3.3, R47.2
unnamed: I2C3.1, R48.2
unnamed: J29.8, R51.1
unnamed: Q7.3, R51.2
unnamed: LS4.-, Q8.3
unnamed: Q8.1, R52.2
RX1: J1.19, J8.6
RX2: J9.19, J16.6
RX3: J17.19, J24.6
RX4: J25.19, J32.6
SCL: J1.14, J4.3, J6.4, R7.1, U2.9
SCL1: J9.14, J12.3, J14.4, R21.1, U1.9
SCL2: J17.14, J20.3, J22.4, R34.1, U4.9
SCL3: J25.14, J28.3, J30.4, R47.1, U7.9
SDA: J1.12, J4.4, J6.3, R8.1, U2.7
SDA1: J9.12, J12.4, J14.3, R22.1, U1.7
SDA2: J17.12, J20.4, J22.3, R35.1, U4.7
SDA3: J25.12, J28.4, J30.3, R48.1, U7.7
SPI_CIPO: J1.61, J2.DO, J5.28
SPI_CIPO1: J9.61, J10.DO, J13.28
SPI_CIPO2: J17.61, J18.DO, J21.28
SPI_CIPO3: J25.61, J26.DO, J29.28
SPI_COPI: J1.59, J2.DI, J5.39
SPI_COPI1: J9.59, J10.DI, J13.39
SPI_COPI2: J17.59, J18.DI, J21.39
SPI_COPI3: J25.59, J26.DI, J29.39
SPI_SCK: J1.57, J2.SCLK, J5.33
SPI_SCK1: J9.57, J10.SCLK, J13.33
SPI_SCK2: J17.57, J18.SCLK, J21.33
SPI_SCK3: J25.57, J26.SCLK, J29.33
SWDCK: J1.21, J7.4, TP1.P$1
SWDCK1: J9.21, J15.4, TP2.P$1
SWDCK2: J17.21, J23.4, TP3.P$1
SWDCK3: J25.21, J31.4, TP4.P$1
SWDIO: J1.23, J7.2
SWDIO1: J9.23, J15.2
SWDIO2: J17.23, J23.2
SWDIO3: J25.23, J31.2
TX1: J1.17, J8.7
TX2: J9.17, J16.7
TX3: J17.17, J24.7
TX4: J25.17, J32.7
USB_D+: J1.3, J3.A6, J3.B6
USB_D+1: J9.3, J11.A6, J11.B6
USB_D+2: J17.3, J19.A6, J19.B6
USB_D+3: J25.3, J27.A6, J27.B6
USB_D-: J1.5, J3.A7, J3.B7
USB_D-1: J9.5, J11.A7, J11.B7
USB_D-2: J17.5, J19.A7, J19.B7
USB_D-3: J25.5, J27.A7, J27.B7
VIN: BYP.2, C1.1, C2.+, C13.1, F2.2, J1.9, R5.2, U5.8
VIN1: BYP1.2, C8.1, C10.1, C11.+, F1.2, J9.9, R18.2, U3.8
VIN2: BYP2.2, C19.1, C21.1, C22.+, F3.2, J17.9, R31.2, U6.8
VIN3: BYP3.2, C28.1, C30.1, C31.+, F4.2, J25.9, R44.2, U8.8
V_USB: BYP.1, F2.1, J3.VBUS1, J3.VBUS2, J8.1
V_USB1: BYP1.1, F1.1, J11.VBUS1, J11.VBUS2, J16.1
V_USB2: BYP2.1, F3.1, J19.VBUS1, J19.VBUS2, J24.1
V_USB3: BYP3.1, F4.1, J27.VBUS1, J27.VBUS2, J32.1

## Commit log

2020-07-28 Pre-review changes
    Added SWD connector
    Updated SPI names
2020-07-29 Post review changes
    - Added notes for jumpers
    - Changed SPI_CS to SD_CS label
    - Connected display reset to IO
    - Added NO jumper between MicroMod and regulator enable
    - Added Buzzer to PWM1
    - Broke out A0/1, RX1/TX1, CAN-RX/TX, 3.3V, and GND
2020-07-30 QC Fixes
2020-08-17 v01 update
    -Added 10ohm resistor to backlight
    -Added 10k pullup to tft reset
    -Connected Attiny reset to MM reset
2020-08-18 v10
    Moved display cable back slightly
    Moved A and B buttons closer together
    Moved measures jumper away from button A
    Added silk to display outline
2020-08-19 v10 post review changes
    -Added 5V/V_USB pin
    -Added BJT to buzzer
    -Replaced pull up/down resistors from 10lk to 100k
    -Replaced 1/10W 10ohm resistor with 1/4W 10ohm
    -Removed display outline on tPlace layer
2020-08-19 v10 cleanup
    -Updated active low labels
    -Fixed Attiny I2C address
    -Updated measures layer
2020-08-20 QC fixes
    - Added note for MEAS jumper
    - Adjusted button B label
2020-08-20 Added production files
2020-08-25 Updated Bottom Stencil for MM connector
2020-09-10 v11
    Updated MM conenctor SPI pins
2020-09-16 Added V11 panel

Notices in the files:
parts and their libraries:
SparkFun-Jumpers: Licensing: Creative Commons ShareAlike 4.0 International - https://creativecommons.org/licenses/by-sa/4.0
SparkFun-Aesthetics: Released under the Creative Commons Attribution Share-Alike 4.0 License
SparkFun-Aesthetics: https://creativecommons.org/licenses/by-sa/4.0
